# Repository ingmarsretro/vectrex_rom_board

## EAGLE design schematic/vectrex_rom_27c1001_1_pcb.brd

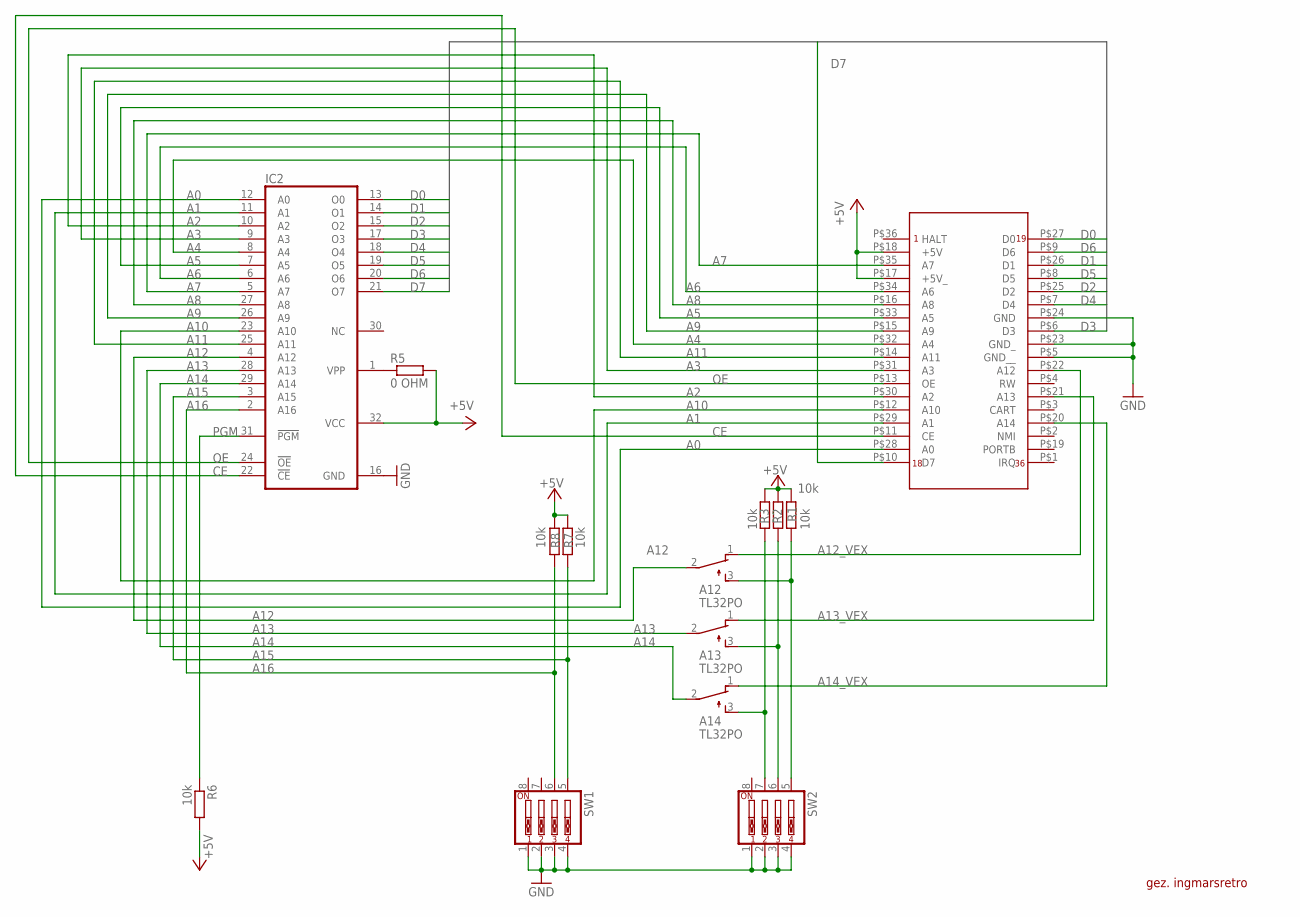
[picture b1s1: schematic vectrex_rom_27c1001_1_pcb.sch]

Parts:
A12, A13, A14: TL32PO; TL3XPO
IC2: 27C1001A; DIL32
R1, R2, R3, R6, R7, R8: 10k; R0805
R5: 0 OHM; R0805
SW1, SW2: SW_DIP-4; EDG-04
U$1: VECTREX_ROMCONNECTOR; ROM_CONNECTOR_PCB

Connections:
+5V: IC2.32 (VCC), R1.2, R2.1, R3.1, R5.2, R6.2, R7.2, R8.2, U$1.P$17 (+5V_), U$1.P$18 (+5V)
A0: IC2.12 (A0), U$1.P$28 (A0)
A1: IC2.11 (A1), U$1.P$29 (A1)
A2: IC2.10 (A2), U$1.P$30 (A2)
A3: IC2.9 (A3), U$1.P$31 (A3)
A4: IC2.8 (A4), U$1.P$32 (A4)
A5: IC2.7 (A5), U$1.P$33 (A5)
A6: IC2.6 (A6), U$1.P$34 (A6)
A7: IC2.5 (A7), U$1.P$35 (A7)
A8: IC2.27 (A8), U$1.P$16 (A8)
A9: IC2.26 (A9), U$1.P$15 (A9)
A10: IC2.23 (A10), U$1.P$12 (A10)
A11: IC2.25 (A11), U$1.P$14 (A11)
A12: A12.2, IC2.4 (A12)
A12_VEX: A12.1 (O), U$1.P$22 (A12)
A13: A13.2, IC2.28 (A13)
A13_VEX: A13.1 (O), U$1.P$21 (A13)
A14: A14.2, IC2.29 (A14)
A14_VEX: A14.1 (O), U$1.P$20 (A14)
A15: IC2.3 (A15), R7.1, SW1.5
A16: IC2.2 (A16), R8.1, SW1.6
CE: IC2.22 (!CE), U$1.P$11 (CE)
D0: IC2.13 (O0), U$1.P$27 (D0)
D1: IC2.14 (O1), U$1.P$26 (D1)
D2: IC2.15 (O2), U$1.P$25 (D2)
D3: IC2.17 (O3), U$1.P$6 (D3)
D4: IC2.18 (O4), U$1.P$7 (D4)
D5: IC2.19 (O5), U$1.P$8 (D5)
D6: IC2.20 (O6), U$1.P$9 (D6)
D7: IC2.21 (O7), U$1.P$10 (D7)
GND: IC2.16 (GND), SW1.1, SW1.2, SW1.3, SW1.4, SW2.1, SW2.2, SW2.3, SW2.4, U$1.P$5 (GND__), U$1.P$23 (GND_), U$1.P$24 (GND)
unnamed: A12.3 (S), R1.1, SW2.5
unnamed: A13.3 (S), R2.2, SW2.6
unnamed: A14.3 (S), R3.2, SW2.7
unnamed: IC2.1 (VPP), R5.1
OE: IC2.24 (!OE), U$1.P$13 (OE)
PGM: IC2.31 (!PGM), R6.1

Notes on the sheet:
gez. ingmarsretro

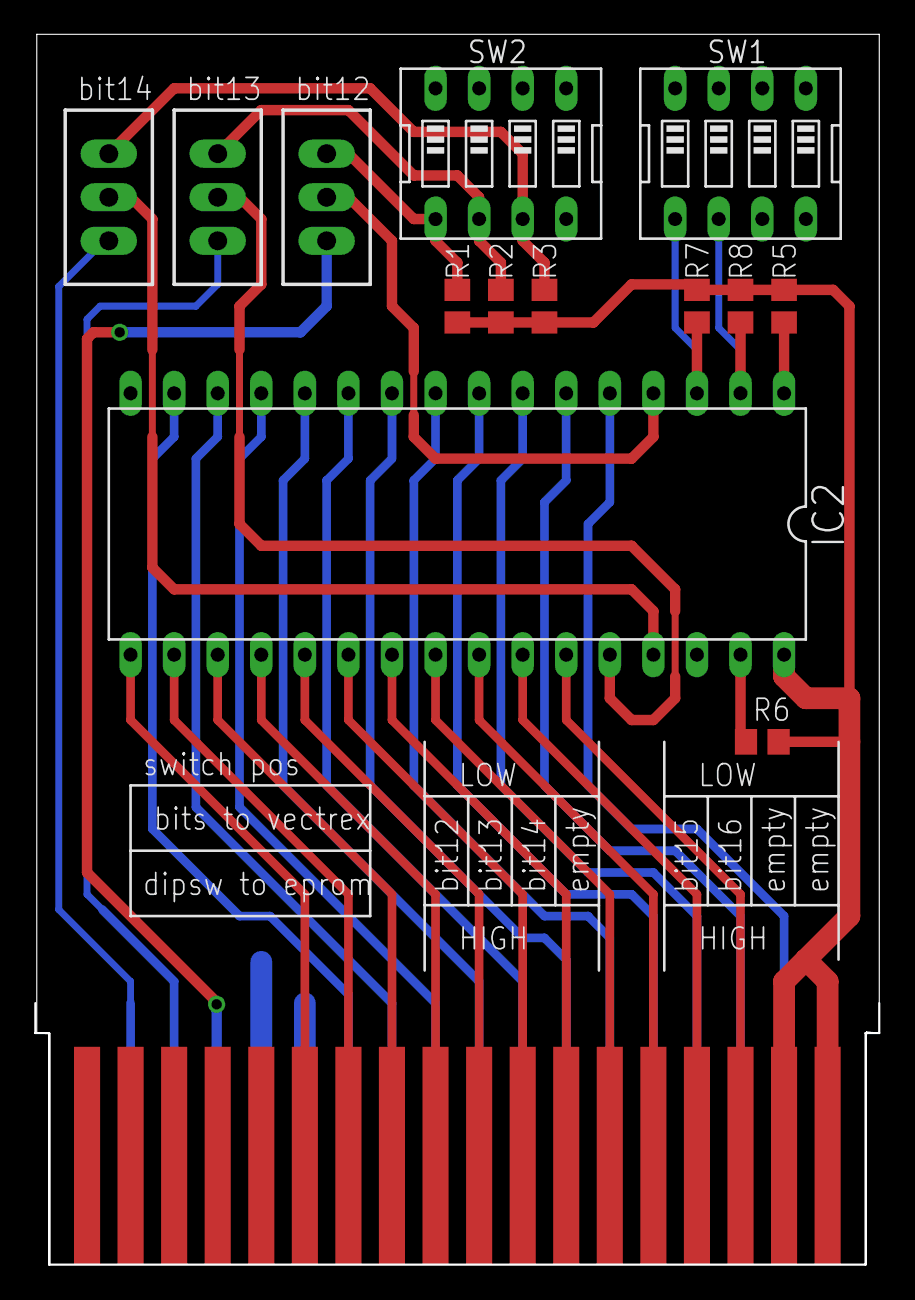
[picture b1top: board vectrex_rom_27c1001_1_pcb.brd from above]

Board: 2 copper layers, 49.2 x 71.7 mm, 14 parts (0 on the bottom side), 37 nets.
